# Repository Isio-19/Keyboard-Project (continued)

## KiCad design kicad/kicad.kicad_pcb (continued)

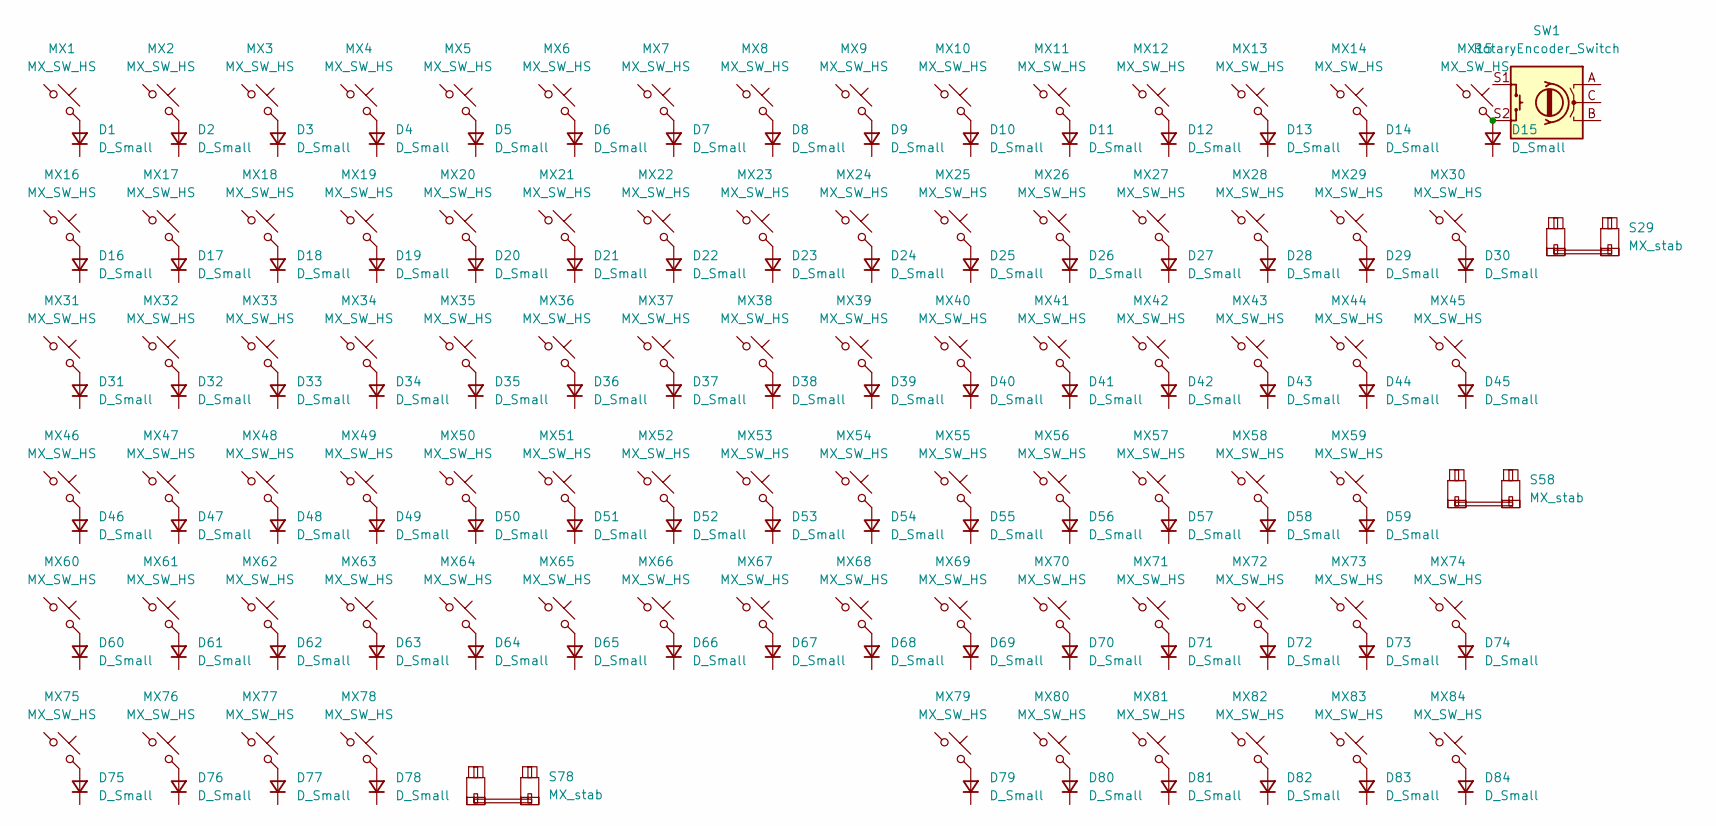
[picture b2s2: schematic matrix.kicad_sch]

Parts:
D1, D2, D3, D4, D5, D6, D7, D8, D9, D10, D11, D12, D13, D14, D15, D16, D17, D18, D19, D20, D21, D22, D23, D24, D25, D26, D27, D28, D29, D30, D31, D32, D33, D34, D35, D36, D37, D38, D39, D40, D41, D42, D43, D44, D45, D46, D47, D48, D49, D50, D51, D52, D53, D54, D55, D56, D57, D58, D59, D60, D61, D62, D63, D64, D65, D66, D67, D68, D69, D70, D71, D72, D73, D74, D75, D76, D77, D78, D79, D80, D81, D82, D83, D84: D_Small; D_SOD-123
MX1, MX2, MX3, MX4, MX5, MX6, MX7, MX8, MX9, MX10, MX11, MX12, MX13, MX14, MX15, MX16, MX17, MX18, MX19, MX20, MX21, MX22, MX23, MX24, MX25, MX26, MX27, MX28, MX29, MX30, MX31, MX32, MX33, MX34, MX35, MX36, MX37, MX38, MX39, MX40, MX41, MX42, MX43, MX44, MX45, MX46, MX47, MX48, MX49, MX50, MX51, MX52, MX53, MX54, MX55, MX56, MX57, MX58, MX59, MX60, MX61, MX62, MX63, MX64, MX65, MX66, MX67, MX68, MX69, MX70, MX71, MX72, MX73, MX74, MX75, MX76, MX77, MX78, MX79, MX80, MX81, MX82, MX83, MX84: MX_SW_HS; SW_MX_HS_CPG151101S11_1u
S29: MX_stab; STAB_MX_P_2u
S58: MX_stab; STAB_MX_P_2.25u
S78: MX_stab; STAB_MX_P_6.25u
SW1: RotaryEncoder_Switch; RotaryEncoder_Alps_EC11E-Switch_Vertical_H20mm

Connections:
unnamed: D2.2 (A), MX2.2
unnamed: D3.2 (A), MX3.2
unnamed: D4.2 (A), MX4.2
unnamed: D5.2 (A), MX5.2
unnamed: D6.2 (A), MX6.2
unnamed: D7.2 (A), MX7.2
unnamed: D8.2 (A), MX8.2
unnamed: D9.2 (A), MX9.2
unnamed: D10.2 (A), MX10.2
unnamed: D11.2 (A), MX11.2
unnamed: D12.2 (A), MX12.2
unnamed: D13.2 (A), MX13.2
unnamed: D14.2 (A), MX14.2
unnamed: D16.2 (A), MX16.2
unnamed: D17.2 (A), MX17.2
unnamed: D18.2 (A), MX18.2
unnamed: D19.2 (A), MX19.2
unnamed: D20.2 (A), MX20.2
unnamed: D21.2 (A), MX21.2
unnamed: D22.2 (A), MX22.2
unnamed: D23.2 (A), MX23.2
unnamed: D24.2 (A), MX24.2
unnamed: D25.2 (A), MX25.2
unnamed: D26.2 (A), MX26.2
unnamed: D27.2 (A), MX27.2
unnamed: D28.2 (A), MX28.2
unnamed: D29.2 (A), MX29.2
unnamed: D30.2 (A), MX30.2
unnamed: D31.2 (A), MX31.2
unnamed: D32.2 (A), MX32.2
unnamed: D33.2 (A), MX33.2
unnamed: D34.2 (A), MX34.2
unnamed: D35.2 (A), MX35.2
unnamed: D36.2 (A), MX36.2
unnamed: D37.2 (A), MX37.2
unnamed: D38.2 (A), MX38.2
unnamed: D39.2 (A), MX39.2
unnamed: D40.2 (A), MX40.2
unnamed: D41.2 (A), MX41.2
unnamed: D42.2 (A), MX42.2
unnamed: D43.2 (A), MX43.2
unnamed: D44.2 (A), MX44.2
unnamed: D45.2 (A), MX45.2
unnamed: D46.2 (A), MX46.2
unnamed: D47.2 (A), MX47.2
unnamed: D48.2 (A), MX48.2
unnamed: D49.2 (A), MX49.2
unnamed: D50.2 (A), MX50.2
unnamed: D51.2 (A), MX51.2
unnamed: D52.2 (A), MX52.2
unnamed: D53.2 (A), MX53.2
unnamed: D54.2 (A), MX54.2
unnamed: D55.2 (A), MX55.2
unnamed: D56.2 (A), MX56.2
unnamed: D57.2 (A), MX57.2
unnamed: D58.2 (A), MX58.2
unnamed: D59.2 (A), MX59.2
unnamed: D60.2 (A), MX60.2
unnamed: D61.2 (A), MX61.2
unnamed: D62.2 (A), MX62.2
unnamed: D63.2 (A), MX63.2
unnamed: D64.2 (A), MX64.2
unnamed: D65.2 (A), MX65.2
unnamed: D66.2 (A), MX66.2
unnamed: D67.2 (A), MX67.2
unnamed: D68.2 (A), MX68.2
unnamed: D69.2 (A), MX69.2
unnamed: D70.2 (A), MX70.2
unnamed: D71.2 (A), MX71.2
unnamed: D72.2 (A), MX72.2
unnamed: D73.2 (A), MX73.2
unnamed: D74.2 (A), MX74.2
unnamed: D75.2 (A), MX75.2
unnamed: D76.2 (A), MX76.2
unnamed: D77.2 (A), MX77.2
unnamed: D78.2 (A), MX78.2
unnamed: D79.2 (A), MX79.2
unnamed: D80.2 (A), MX80.2
unnamed: D81.2 (A), MX81.2
unnamed: D82.2 (A), MX82.2
unnamed: D83.2 (A), MX83.2
unnamed: D84.2 (A), MX84.2

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
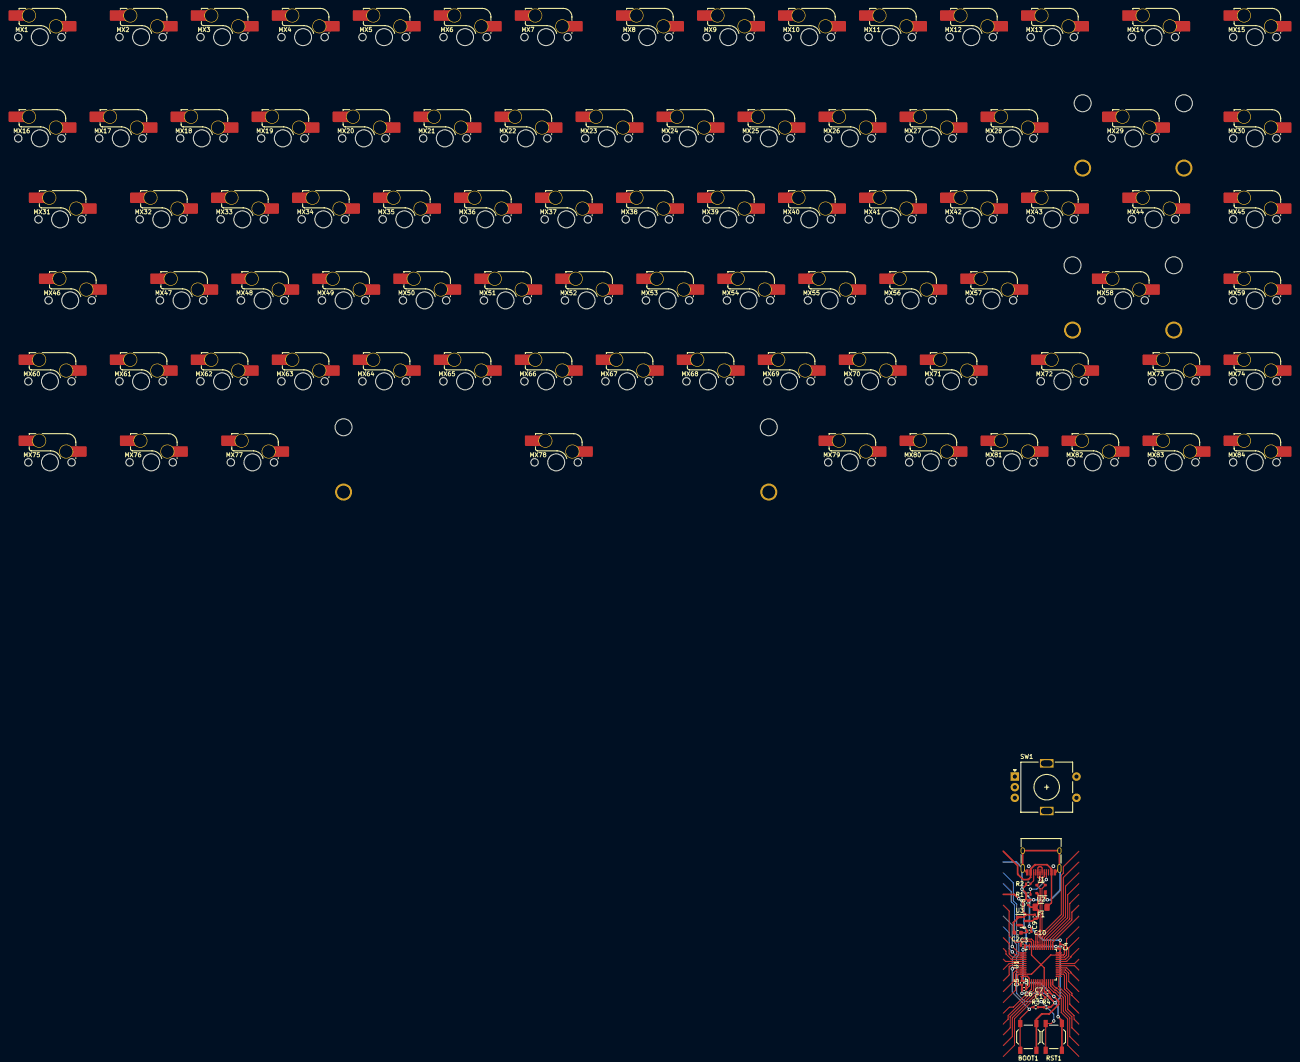
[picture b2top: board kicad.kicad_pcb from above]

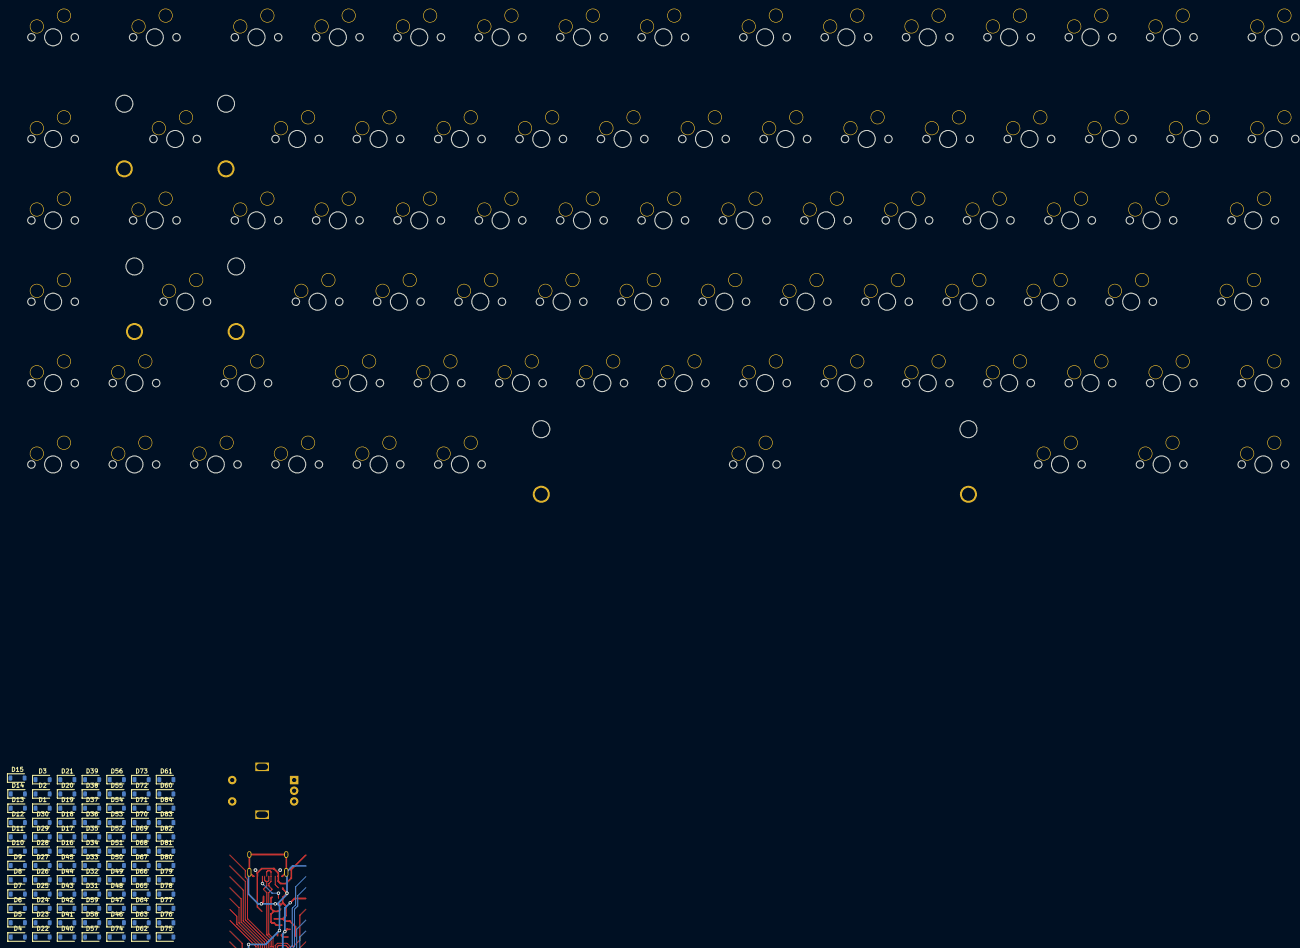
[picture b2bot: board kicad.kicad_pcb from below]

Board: 2 copper layers, 193 parts (84 on the bottom side), 95 nets.

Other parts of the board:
S17: MX_stab; STAB_MX_P_2u
S47: MX_stab; STAB_MX_P_2.25u
S81: MX_stab; STAB_MX_P_6.25u

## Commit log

2023-11-06 Initial push & Finished schematics
2023-11-06 Added footprints to components
2023-11-06 Basics schematics done, PCB design started
2024-08-17 Removed: all files, restarting project
2024-08-17 Added: footprint libraries
2024-08-17 Added: Kicad project start
2024-08-17 Added: footprints libraries for PCB and schematics
2024-08-19 Added: USB C footprint library
2024-08-20 Added: Switch Matrix
2024-08-20 Added: rotary encoder to schematics
2024-08-20 Restart the project, using STM32F072CBT instead of ATmega32U4-AU
2024-08-20 Added: Traces between diode and hotswap socket, and with row
2024-08-20 Changed: switch footprint
2024-08-20 Removed: traces from the template
2024-08-21 Changed: Switch matrix layout
2024-08-21 Added: col and row traces
2024-08-21 Added: wiring to the switch matrix
2024-08-21 Removed: old project version
2024-08-21 Fixed: all clearance violations
2024-08-21 Finished: base keybaord
2024-08-22 -Added: Ground fill
2024-08-22 Added: Ground fill island
2024-08-23 Added: Stepped CAPS_LOCK and Split backspace
2024-08-23 Added: Skyloong rotary encoder
2024-08-29 Finished: Wiring for the Switch matrix, Underglow RGB and Per-key RGb
2024-09-06 Added: MOSFET for encoder and drill holes for case
2024-09-06 Added: README.md
2024-09-06 Added: ground fill vias
2024-09-06 Added: more ground fill vias
2024-09-06 Added: more ground fill vias and split space bars
2024-09-06 Fixed: Silkscreens overlap
2024-09-06 Saved files
2024-09-06 Removed: old RGB file
2024-09-09 Initial branch commit
2024-09-09 Finished: alt wiring
